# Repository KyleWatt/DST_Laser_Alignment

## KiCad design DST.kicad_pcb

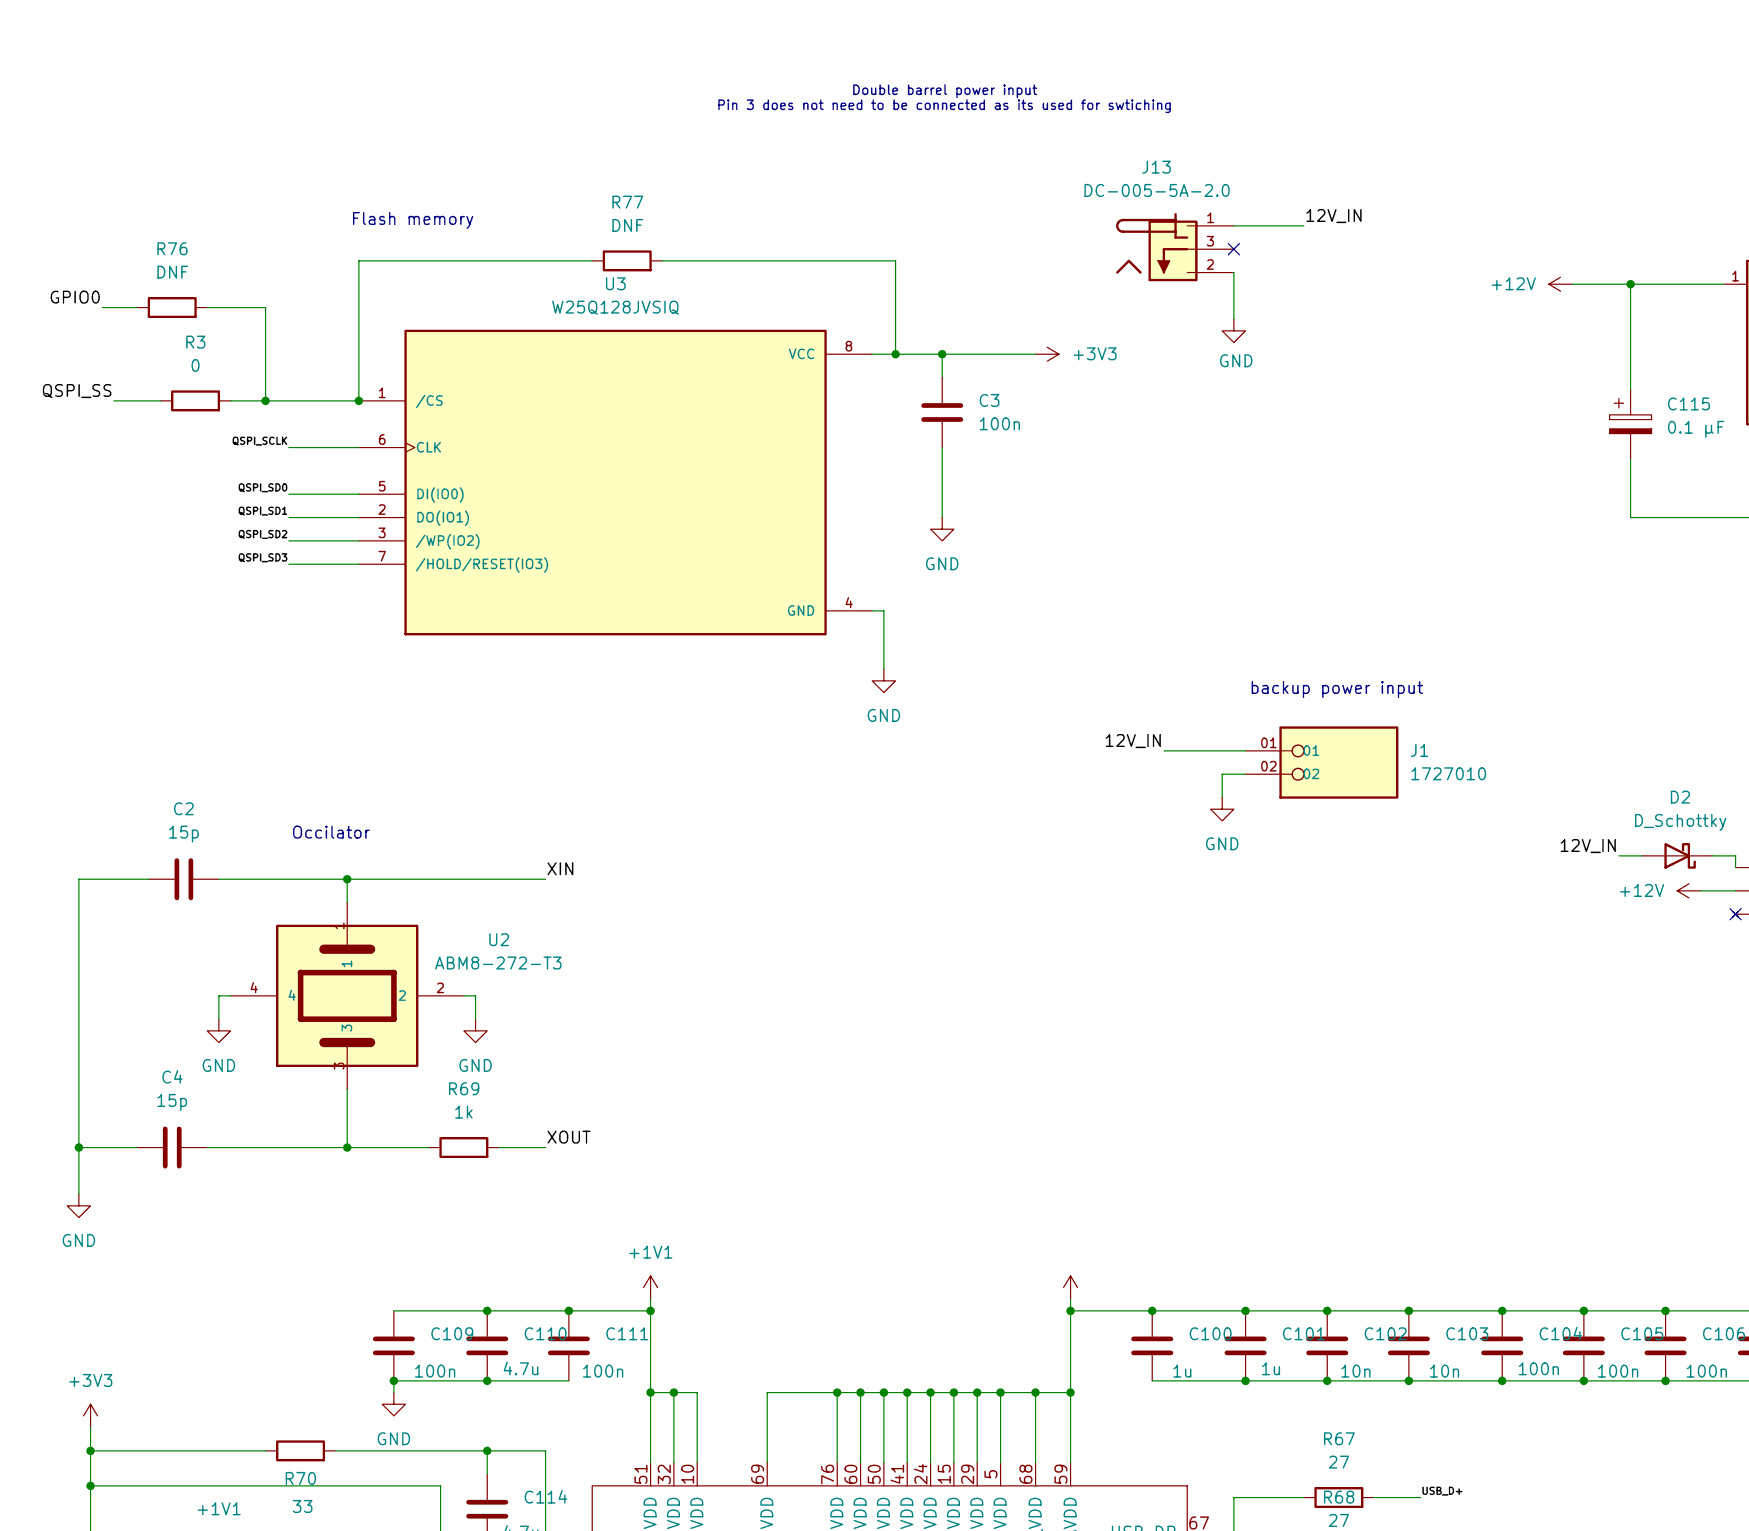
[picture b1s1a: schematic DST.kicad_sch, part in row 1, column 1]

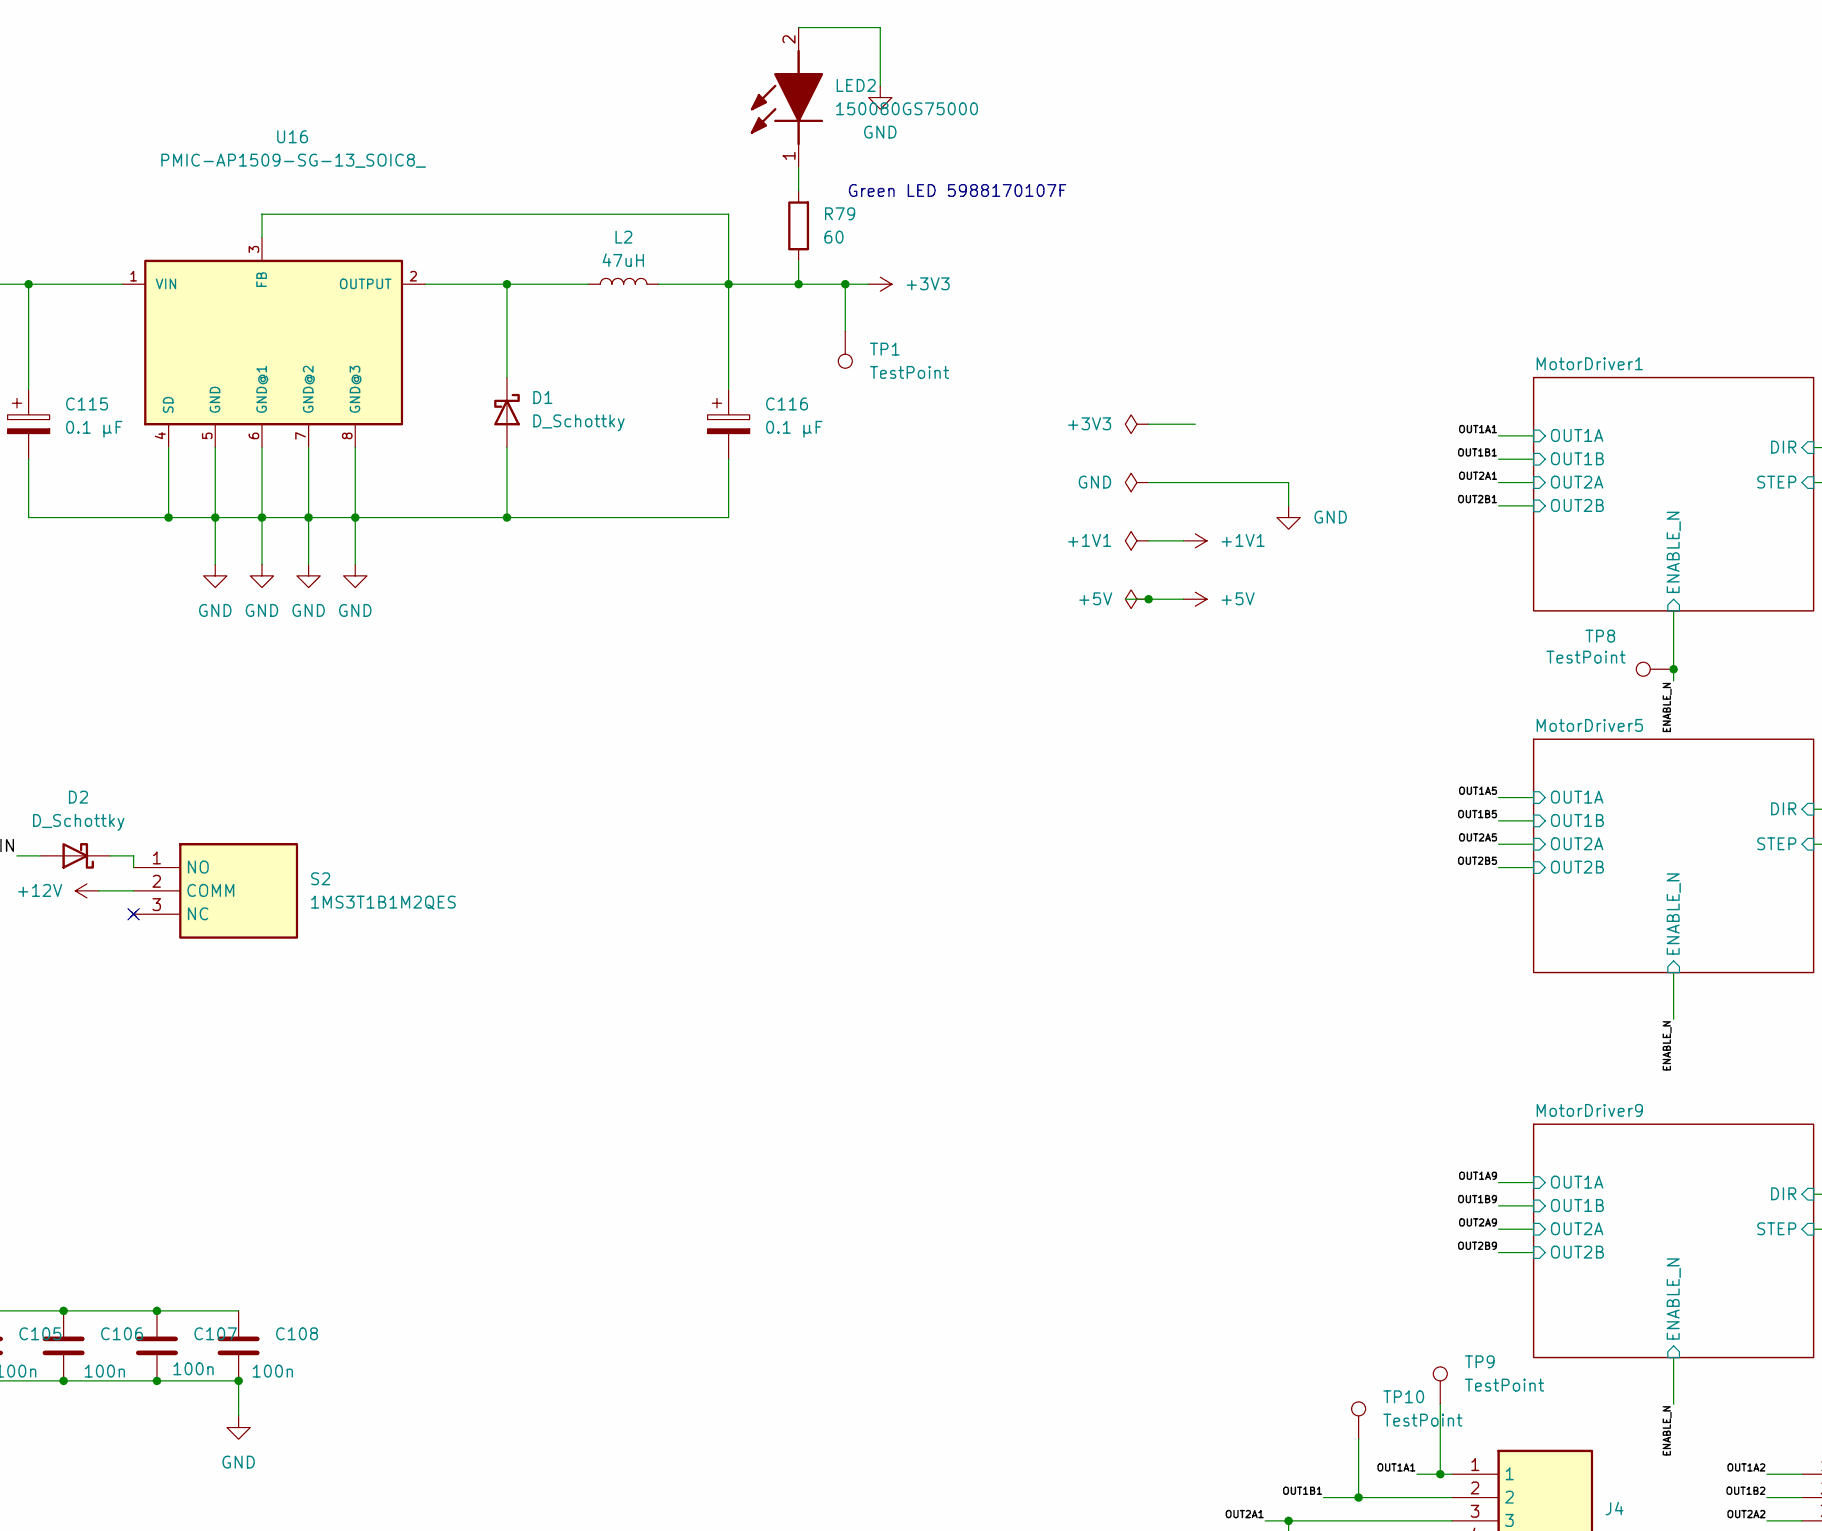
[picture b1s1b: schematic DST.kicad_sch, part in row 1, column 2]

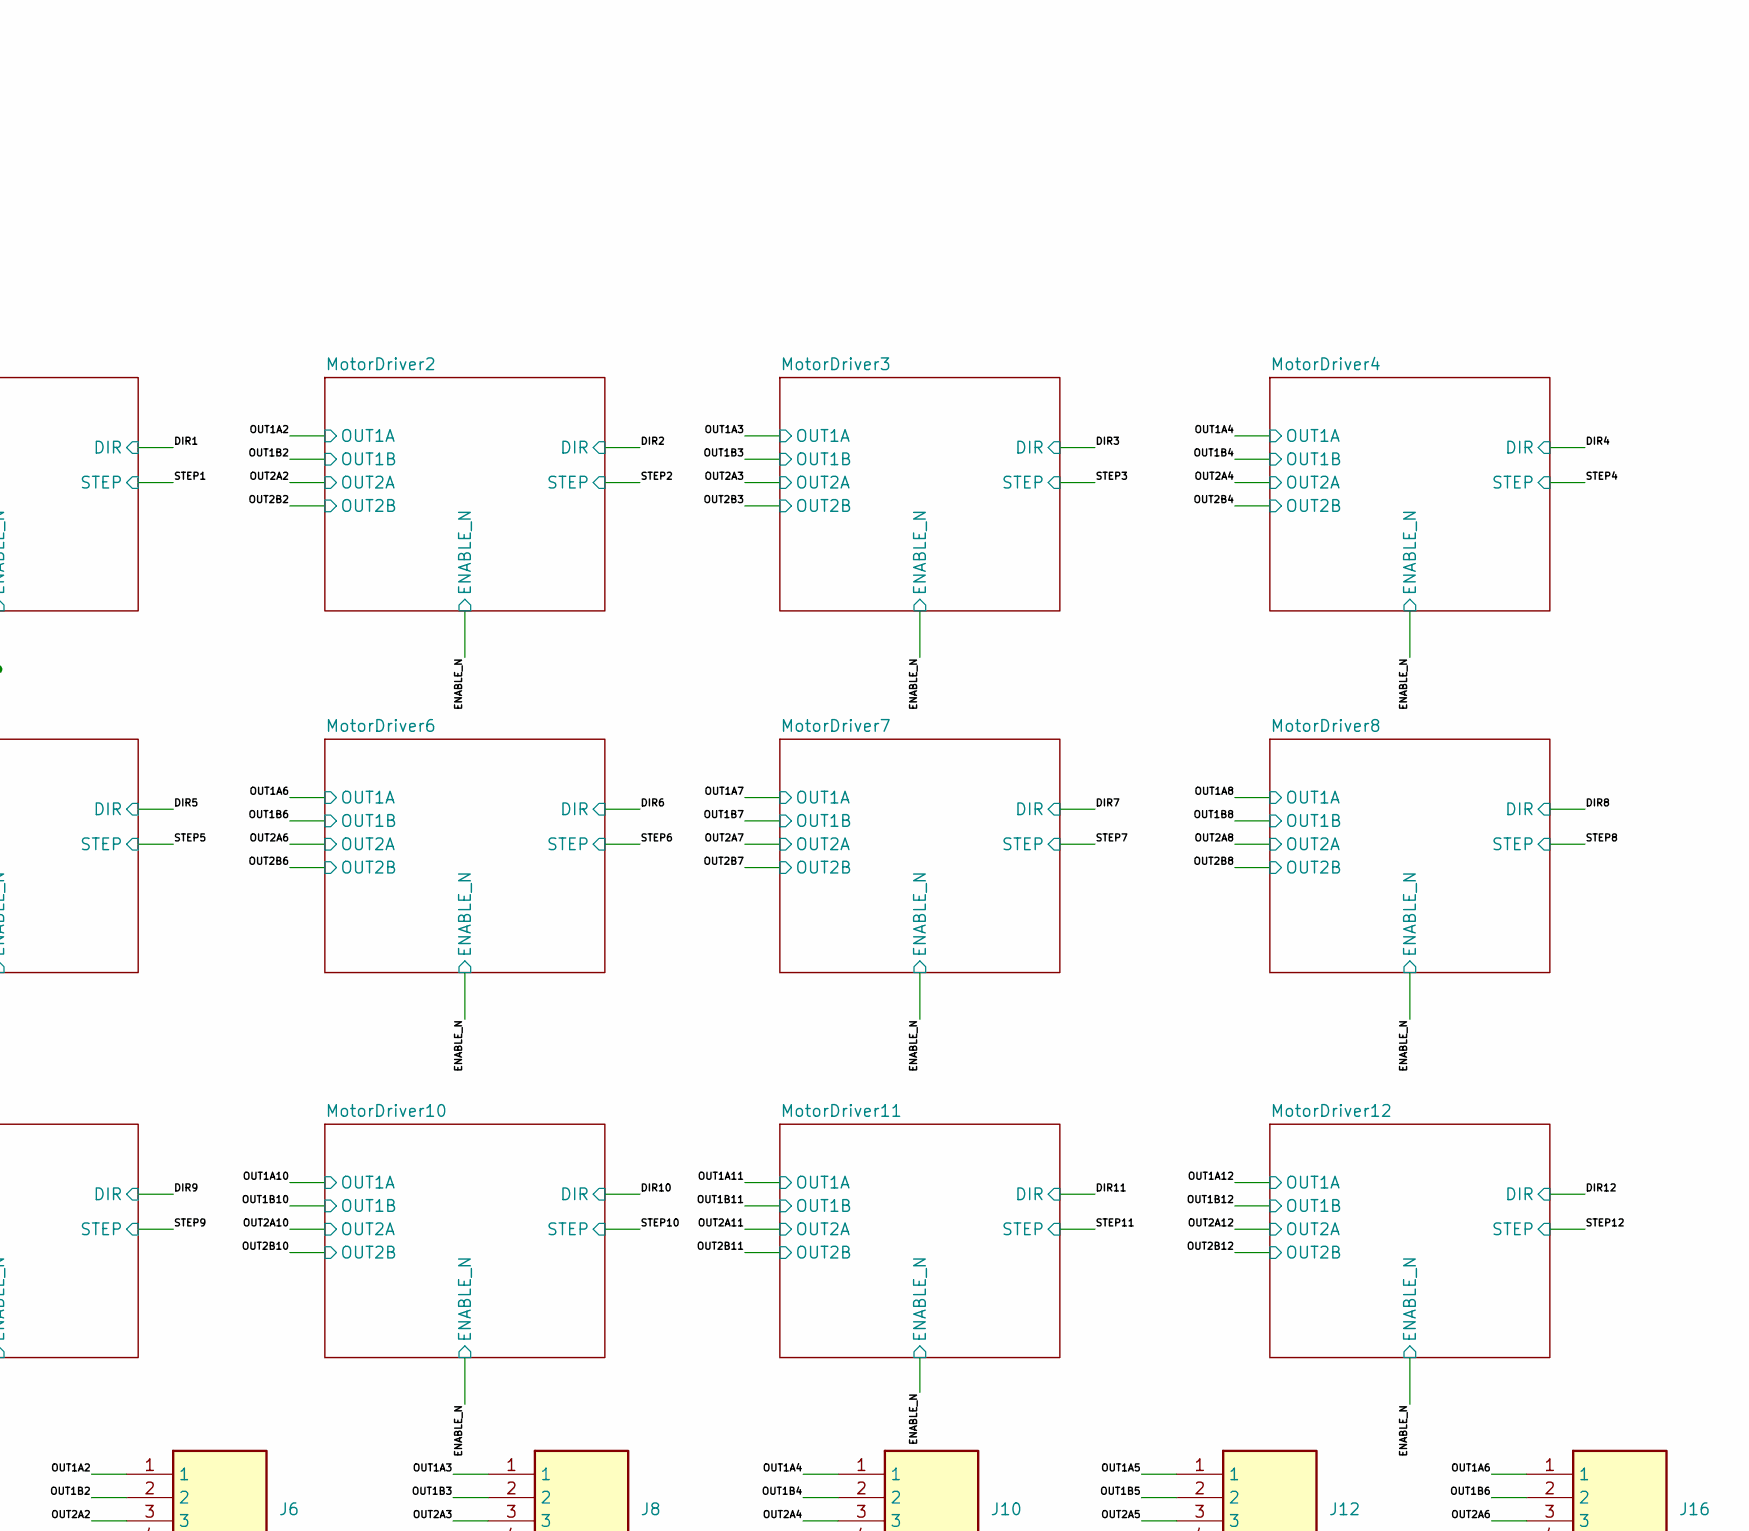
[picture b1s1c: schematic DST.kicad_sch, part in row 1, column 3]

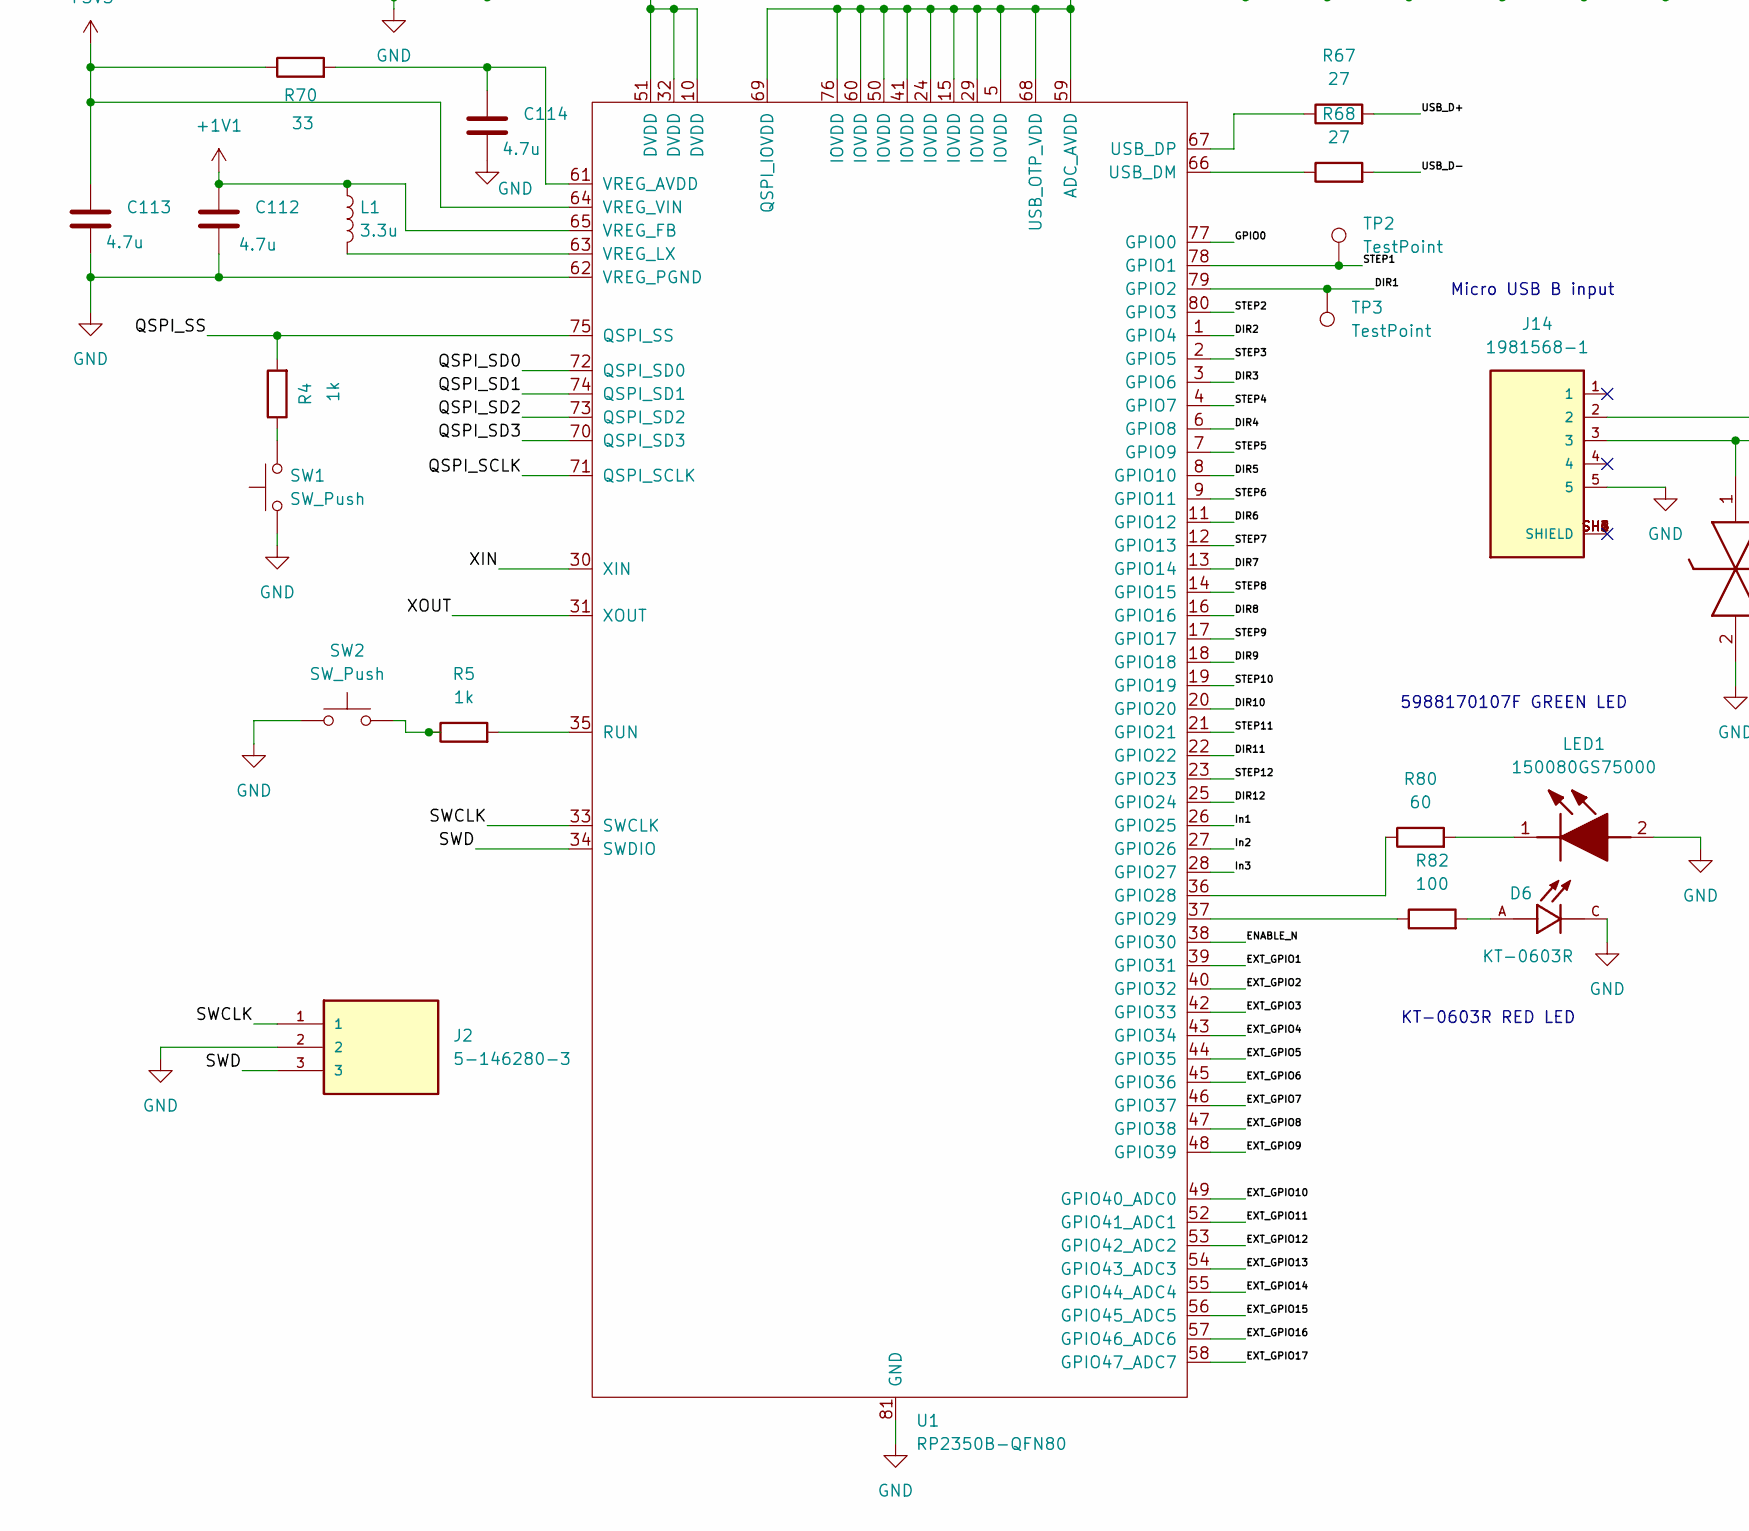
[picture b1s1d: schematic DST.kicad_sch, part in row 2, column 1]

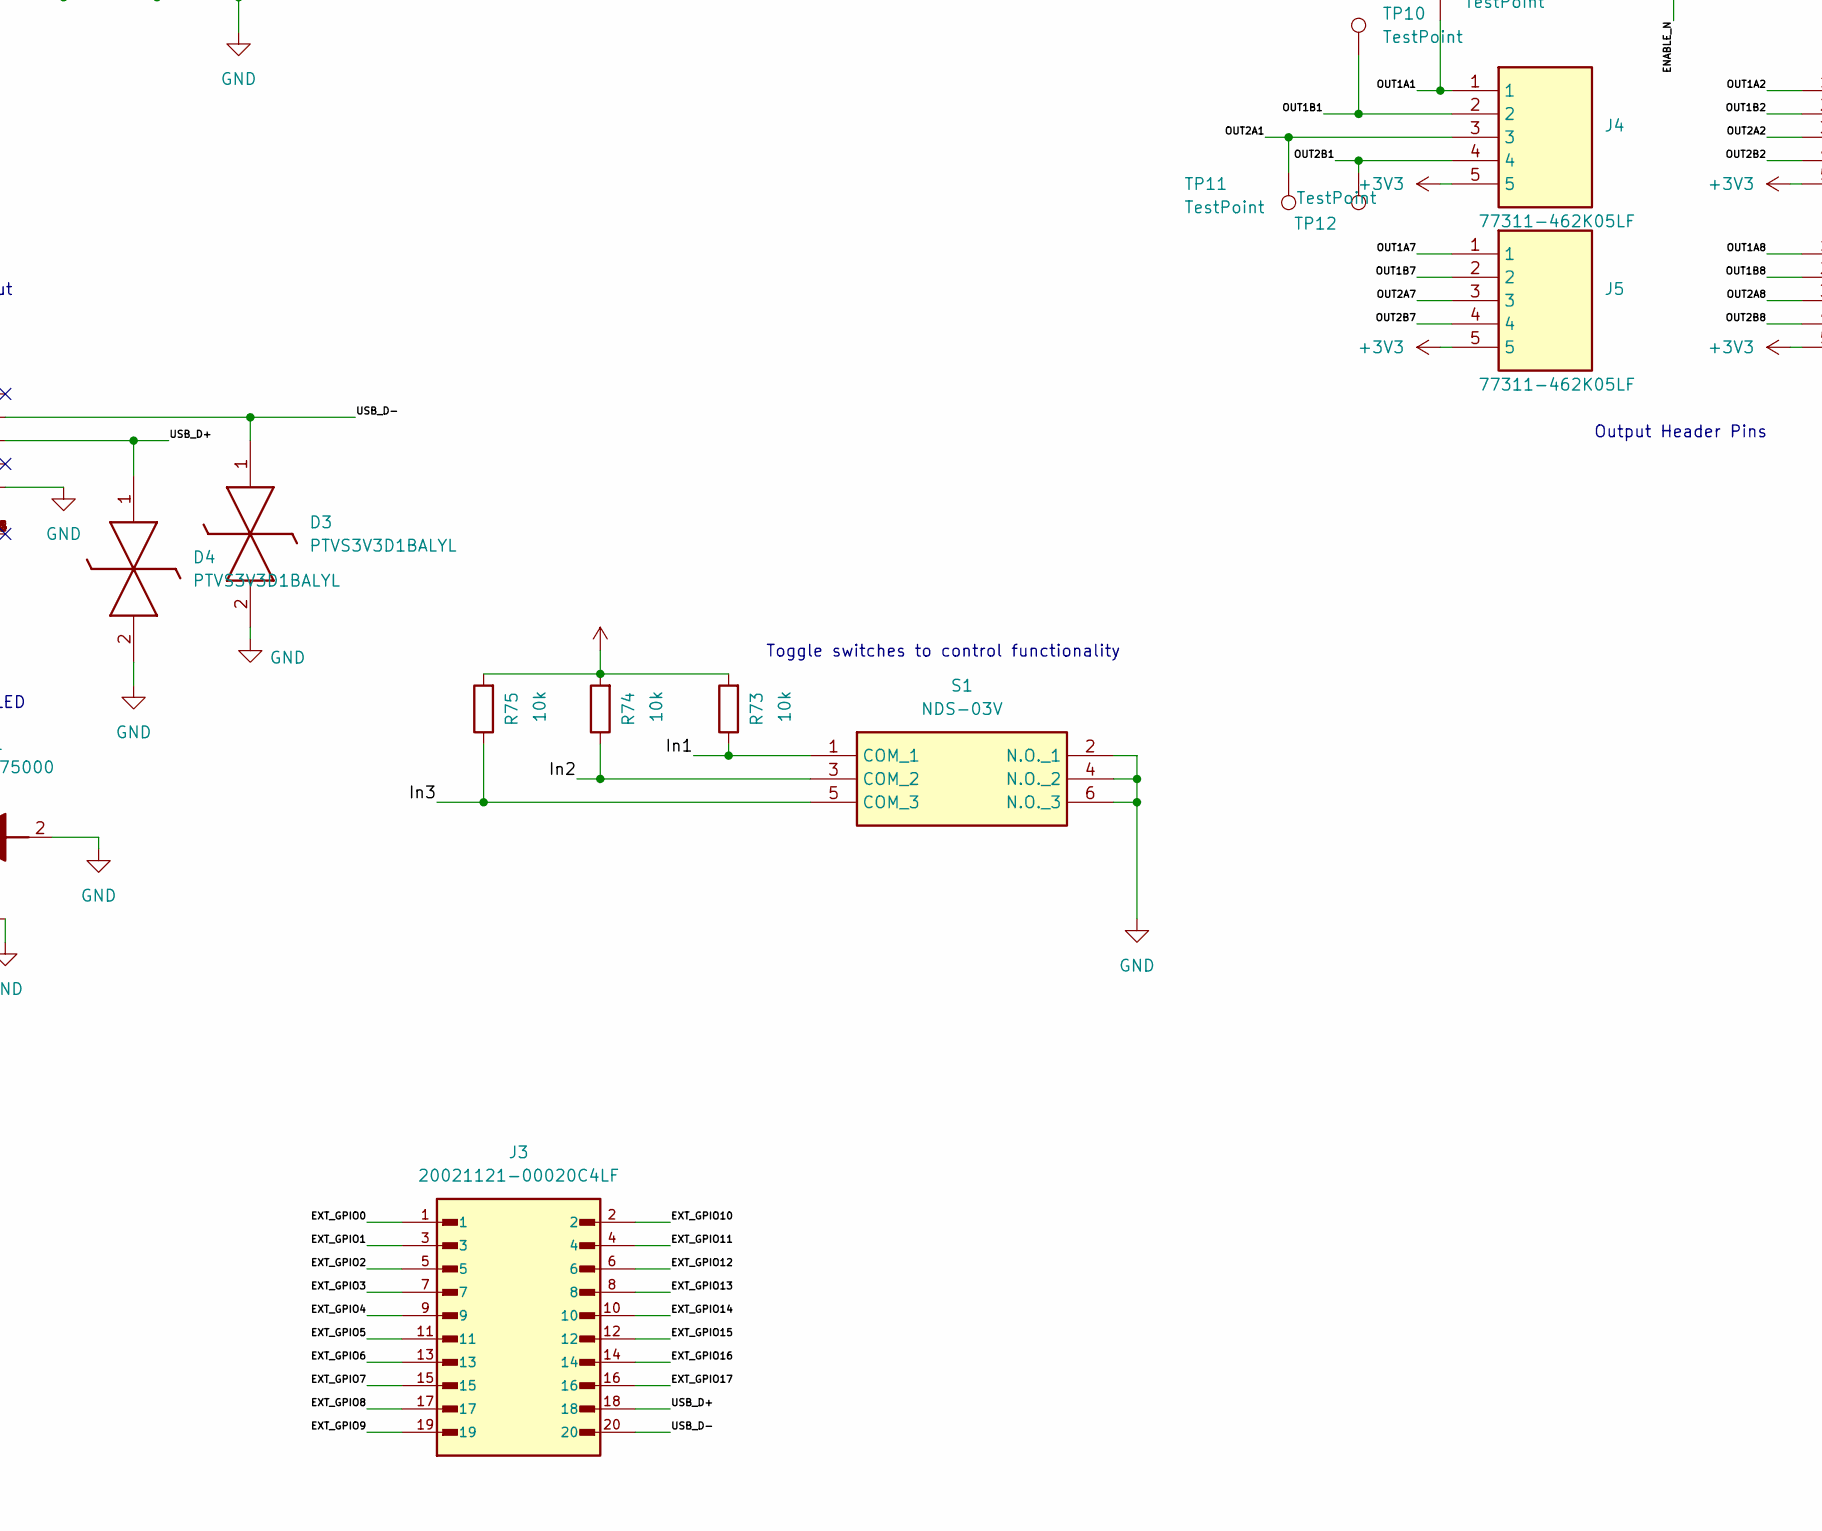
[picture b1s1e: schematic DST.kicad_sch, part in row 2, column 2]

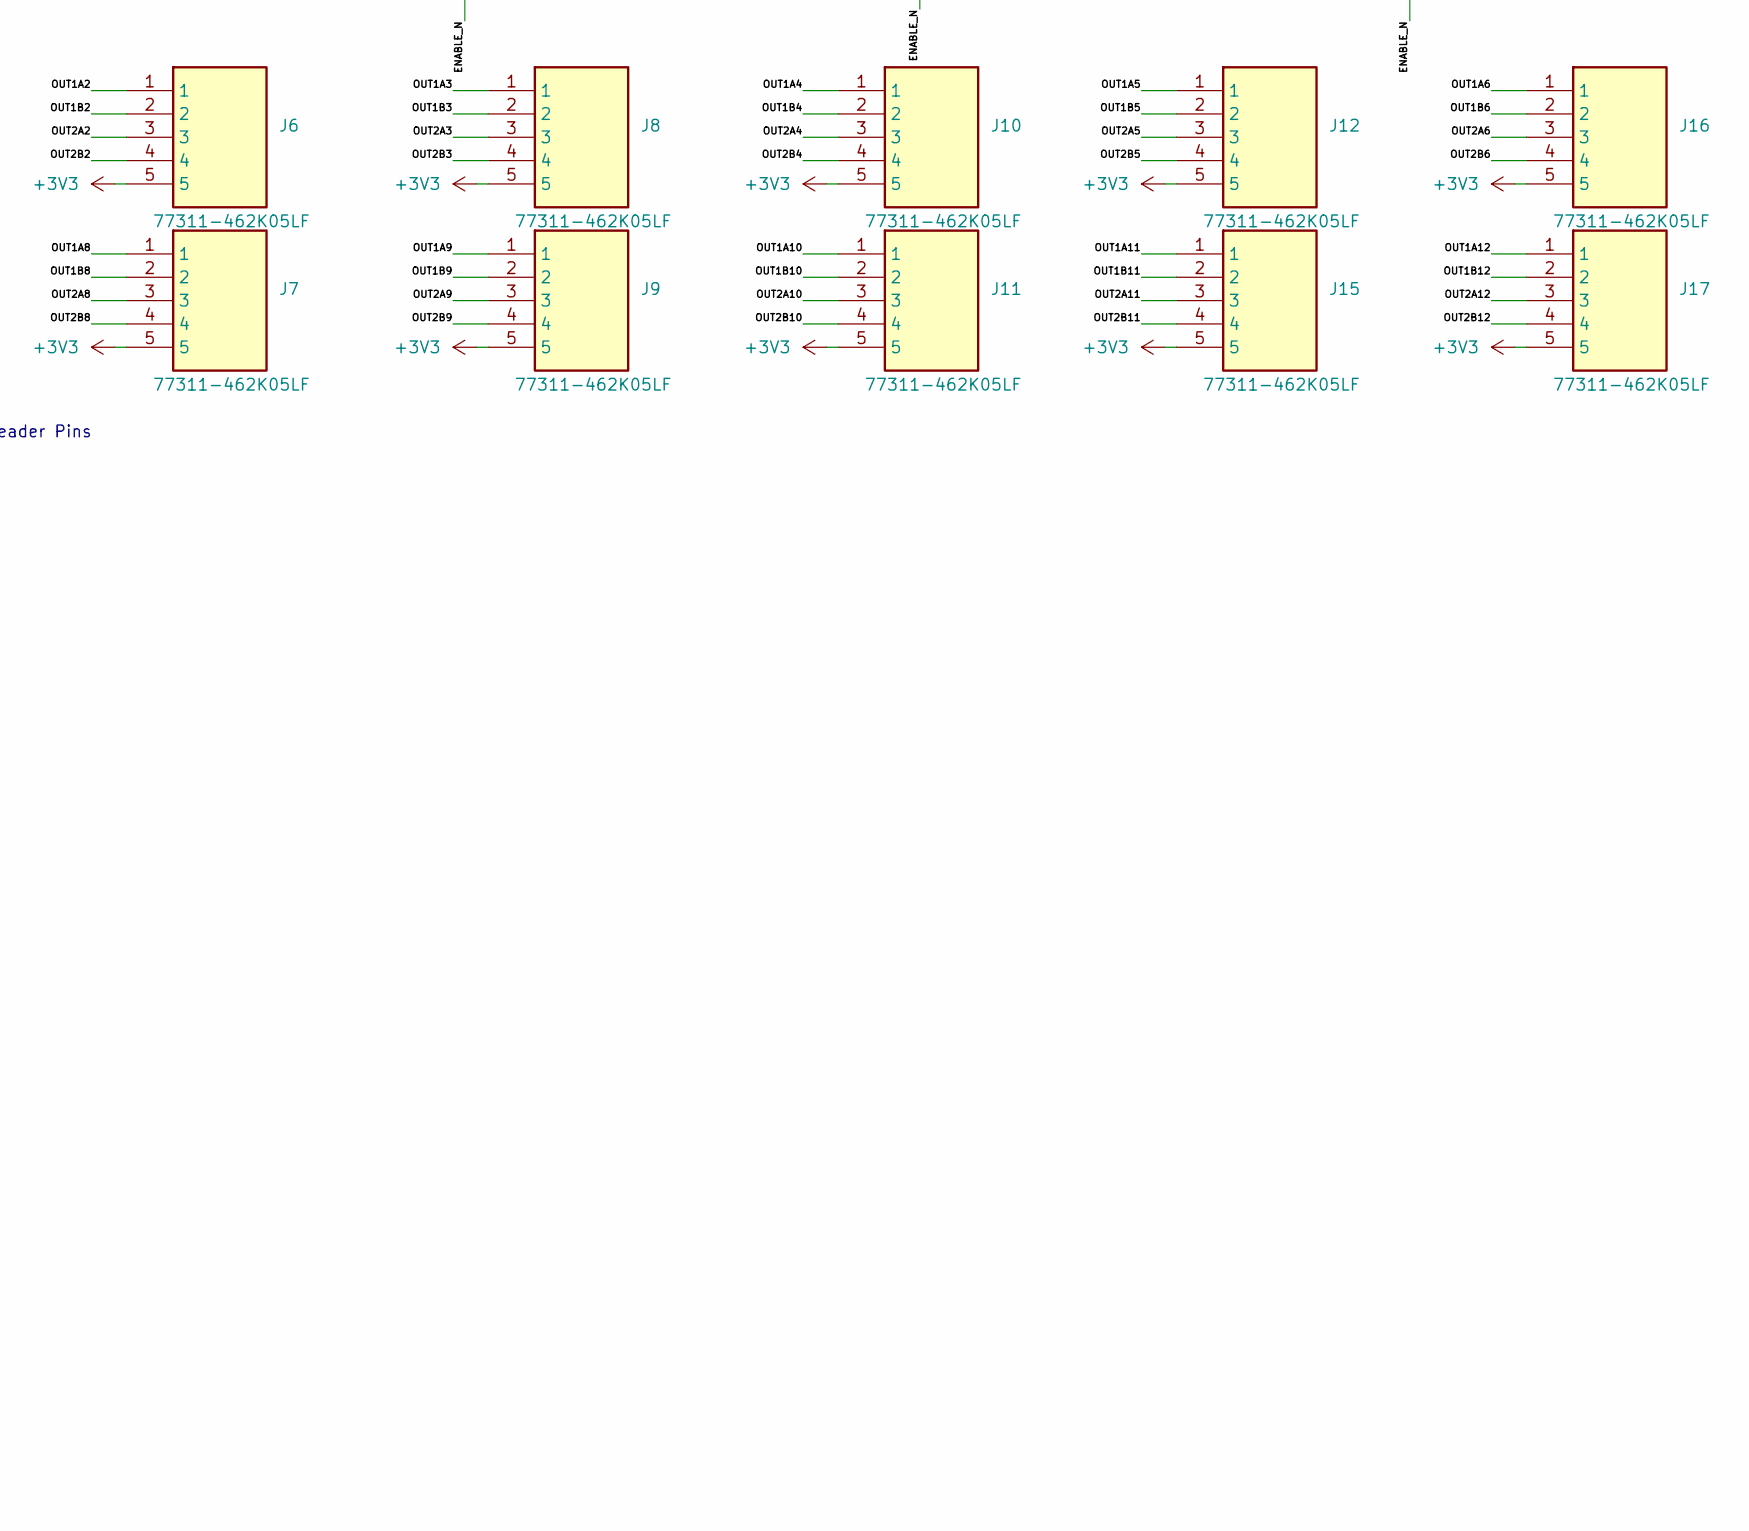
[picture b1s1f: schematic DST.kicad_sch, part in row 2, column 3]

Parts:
C2, C4: 15p; C_0402_1005Metric
C3, C104, C105, C106, C107, C108, C109, C111: 100n; C_0402_1005Metric
C100, C101: 1u; C_0402_1005Metric
C102, C103: 10n; C_0402_1005Metric
C110, C112, C113, C114: 4.7u; C_0402_1005Metric
C115, C116: 0.1 µF; C_0603_1608Metric
D1, D2: D_Schottky; DIOM5436X244N
D3, D4: PTVS3V3D1BALYL; PESD5V0S1BL315; Mouser Part Number 771-PTVS3V3D1BALYL
D6: KT-0603R; LED_KT-0603R; PARTREV 2013/01/24
J1: 1727010; PHOENIX_1727010; PARTREV 03.03.2021
J2: 5-146280-3; TE_5-146280-3; PARTREV R
J3: 20021121-00020C4LF; AMPHENOL_20021121-00020C4LF
J4, J5, J6, J7, J8, J9, J10, J11, J12, J15, J16, J17: 77311-462K05LF; HDRV5W62P0X254_1X5_1270X240X1624P; Manufacturer_Part_Number 77311-462K05LF
J13: DC-005-5A-2.0; XKB_DC-005-5A-2.0; PARTREV A0
J14: 1981568-1; TE_1981568-1; PARTREV E3
L1: 3.3u; L_0402_1005Metric
L2: 47uH; L_0805_2012Metric
LED1, LED2: 150080GS75000; LEDM2012X80N; Mouser Part Number 710-150080GS75000
R3: 0; R_0805_2012Metric
R4, R5, R69: 1k; R_0805_2012Metric
R67, R68: 27; R_0402_1005Metric
R70: 33; R_0805_2012Metric
R73, R74, R75: 10k; R_0402_1005Metric
R76, R77: DNF; R_0805_2012Metric
R79: 60; R_0805_2012Metric
R80: 60; R_0402_1005Metric
R82: 100; R_0402_1005Metric
S1: NDS-03V; NDS03V; Mouser Part Number 113-NDS03V
S2: 1MS3T1B1M2QES; Mouser Part Number 118-1MS3T1B1M2QES
SW1, SW2: SW_Push; SPEH110101
TP1, TP2, TP3, TP8, TP9, TP10, TP11, TP12: TestPoint; TestPoint_Pad_2.0x2.0mm
U1: RP2350B-QFN80; QFN-80-1EP_10x10mm_P0.4mm_EP3.4x3.4mm_ThermalVias
U2: ABM8-272-T3
U3: W25Q128JVSIQ; SOIC127P790X216-8N; PARTREV I
U16: PMIC-AP1509-SG-13_SOIC8_; SOIC8-1.27-5X4MM; MPN AP1509-SG-13

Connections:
+1V1: C109.2, C110.2, C111.2, C112.2, L1.1, U1.10 (DVDD), U1.32 (DVDD), U1.51 (DVDD), U1.65 (VREG_FB)
+3V3: C3.1, C100.2, C101.2, C102.2, C103.2, C104.2, C105.2, C106.2, C107.2, C108.2, C113.2, C116.1, J4.5, J5.5, J6.5, J7.5, J8.5, J9.5, J10.5, J11.5, J12.5, J15.5, J16.5, J17.5, L2.2, R70.1, R73.2, R74.2, R75.2, R77.2, R79.1, TP1.1, U1.5 (IOVDD), U1.15 (IOVDD), U1.24 (IOVDD), U1.29 (IOVDD), U1.41 (IOVDD), U1.50 (IOVDD), U1.59 (ADC_AVDD), U1.60 (IOVDD), U1.64 (VREG_VIN), U1.68 (USB_OTP_VDD), U1.69 (QSPI_IOVDD), U1.76 (IOVDD), U3.8 (VCC), U16.3 (FB); also elsewhere on the board
/12V_IN: D2.2 (A), J1.01, J13.1
/DIR1: TP3.1, U1.79 (GPIO2); also elsewhere on the board
/DIR2: U1.1 (GPIO4); also elsewhere on the board
/DIR3: U1.3 (GPIO6); also elsewhere on the board
/DIR4: U1.6 (GPIO8); also elsewhere on the board
/DIR5: U1.8 (GPIO10); also elsewhere on the board
/DIR6: U1.11 (GPIO12); also elsewhere on the board
/DIR7: U1.13 (GPIO14); also elsewhere on the board
/DIR8: U1.16 (GPIO16); also elsewhere on the board
/DIR9: U1.18 (GPIO18); also elsewhere on the board
/DIR10: U1.20 (GPIO20); also elsewhere on the board
/DIR11: U1.22 (GPIO22); also elsewhere on the board
/DIR12: U1.25 (GPIO24); also elsewhere on the board
/ENABLE_N: TP8.1, U1.38 (GPIO30); also elsewhere on the board
/EXT_GPIO0: J3.1
/EXT_GPIO1: J3.3, U1.39 (GPIO31)
/EXT_GPIO2: J3.5, U1.40 (GPIO32)
/EXT_GPIO3: J3.7, U1.42 (GPIO33)
/EXT_GPIO4: J3.9, U1.43 (GPIO34)
/EXT_GPIO5: J3.11, U1.44 (GPIO35)
/EXT_GPIO6: J3.13, U1.45 (GPIO36)
/EXT_GPIO7: J3.15, U1.46 (GPIO37)
/EXT_GPIO8: J3.17, U1.47 (GPIO38)
/EXT_GPIO9: J3.19, U1.48 (GPIO39)
/EXT_GPIO10: J3.2, U1.49 (GPIO40_ADC0)
/EXT_GPIO11: J3.4, U1.52 (GPIO41_ADC1)
/EXT_GPIO12: J3.6, U1.53 (GPIO42_ADC2)
/EXT_GPIO13: J3.8, U1.54 (GPIO43_ADC3)
/EXT_GPIO14: J3.10, U1.55 (GPIO44_ADC4)
/EXT_GPIO15: J3.12, U1.56 (GPIO45_ADC5)
/EXT_GPIO16: J3.14, U1.57 (GPIO46_ADC6)
/EXT_GPIO17: J3.16, U1.58 (GPIO47_ADC7)
/GPIO0: R76.1, U1.77 (GPIO0)
/In1: R73.1, S1.1 (COM_1), U1.26 (GPIO25)
/In2: R74.1, S1.3 (COM_2), U1.27 (GPIO26)
/In3: R75.1, S1.5 (COM_3), U1.28 (GPIO27)
/OUT1A1: J4.1, TP9.1; also elsewhere on the board
/OUT1A2: J6.1; also elsewhere on the board
/OUT1A3: J8.1; also elsewhere on the board
/OUT1A4: J10.1; also elsewhere on the board
/OUT1A5: J12.1; also elsewhere on the board
/OUT1A6: J16.1; also elsewhere on the board
/OUT1A7: J5.1; also elsewhere on the board
/OUT1A8: J7.1; also elsewhere on the board
/OUT1A9: J9.1; also elsewhere on the board
/OUT1A10: J11.1; also elsewhere on the board
/OUT1A11: J15.1; also elsewhere on the board
/OUT1A12: J17.1; also elsewhere on the board
/OUT1B1: J4.2, TP10.1; also elsewhere on the board
/OUT1B2: J6.2; also elsewhere on the board
/OUT1B3: J8.2; also elsewhere on the board
/OUT1B4: J10.2; also elsewhere on the board
/OUT1B5: J12.2; also elsewhere on the board
/OUT1B6: J16.2; also elsewhere on the board
/OUT1B7: J5.2; also elsewhere on the board
/OUT1B8: J7.2; also elsewhere on the board
/OUT1B9: J9.2; also elsewhere on the board
/OUT1B10: J11.2; also elsewhere on the board
/OUT1B11: J15.2; also elsewhere on the board
/OUT1B12: J17.2; also elsewhere on the board
/OUT2A1: J4.3, TP11.1; also elsewhere on the board
/OUT2A2: J6.3; also elsewhere on the board
/OUT2A3: J8.3; also elsewhere on the board
/OUT2A4: J10.3; also elsewhere on the board
/OUT2A5: J12.3; also elsewhere on the board
/OUT2A6: J16.3; also elsewhere on the board
/OUT2A7: J5.3; also elsewhere on the board
/OUT2A8: J7.3; also elsewhere on the board
/OUT2A9: J9.3; also elsewhere on the board
/OUT2A10: J11.3; also elsewhere on the board
/OUT2A11: J15.3; also elsewhere on the board
/OUT2A12: J17.3; also elsewhere on the board
/OUT2B1: J4.4, TP12.1; also elsewhere on the board
/OUT2B2: J6.4; also elsewhere on the board
/OUT2B3: J8.4; also elsewhere on the board
/OUT2B4: J10.4; also elsewhere on the board
/OUT2B5: J12.4; also elsewhere on the board
/OUT2B6: J16.4; also elsewhere on the board
/OUT2B7: J5.4; also elsewhere on the board
/OUT2B8: J7.4; also elsewhere on the board
/OUT2B9: J9.4; also elsewhere on the board
/OUT2B10: J11.4; also elsewhere on the board
/OUT2B11: J15.4; also elsewhere on the board
/OUT2B12: J17.4; also elsewhere on the board
/QSPI_SCLK: U1.71 (QSPI_SCLK), U3.6 (CLK)
/QSPI_SD0: U1.72 (QSPI_SD0), U3.5 (DI(IO0))
/QSPI_SD1: U1.74 (QSPI_SD1), U3.2 (DO(IO1))
/QSPI_SD2: U1.73 (QSPI_SD2), U3.3 (/WP(IO2))
/QSPI_SD3: U1.70 (QSPI_SD3), U3.7 (/HOLD/RESET(IO3))
/QSPI_SS: R3.1, R4.2, U1.75 (QSPI_SS)
/STEP1: TP2.1, U1.78 (GPIO1); also elsewhere on the board
/STEP2: U1.80 (GPIO3); also elsewhere on the board
/STEP3: U1.2 (GPIO5); also elsewhere on the board
/STEP4: U1.4 (GPIO7); also elsewhere on the board
/STEP5: U1.7 (GPIO9); also elsewhere on the board
/STEP6: U1.9 (GPIO11); also elsewhere on the board
/STEP7: U1.12 (GPIO13); also elsewhere on the board
/STEP8: U1.14 (GPIO15); also elsewhere on the board
/STEP9: U1.17 (GPIO17); also elsewhere on the board
/STEP10: U1.19 (GPIO19); also elsewhere on the board
/STEP11: U1.21 (GPIO21); also elsewhere on the board
/STEP12: U1.23 (GPIO23); also elsewhere on the board
/SWCLK: J2.1, U1.33 (SWCLK)
/SWD: J2.3, U1.34 (SWDIO)
/USB_D+: D4.1 (K1), J3.18, J14.3, R67.2
/USB_D-: D3.1 (K1), J3.20, J14.2, R68.2
/XIN: C2.2, U1.30 (XIN), U2.1
/XOUT: R69.2, U1.31 (XOUT)
GND: C2.1, C3.2, C4.1, C100.1, C101.1, C102.1, C103.1, C104.1, C105.1, C106.1, C107.1, C108.1, C109.1, C110.1, C111.1, C112.1, C113.1, C114.1, C115.2, C116.2, D1.2 (A), D3.2 (K2), D4.2 (K2), D6.C, J1.02, J2.2, J13.2, J14.5, LED1.2 (A), LED2.2 (A), S1.2 (N.O._1), S1.4 (N.O._2), S1.6 (N.O._3), SW1.1, SW2.1, U1.62 (VREG_PGND), U1.81 (GND), U2.2, U2.4, U3.4 (GND), U16.4 (SD), U16.5 (GND), U16.6 (GND@1), U16.7 (GND@2), U16.8 (GND@3); also elsewhere on the board
unnamed: C4.2, R69.1, U2.3
unnamed: D1.1 (K), L2.1, U16.2 (OUTPUT)
unnamed: D6.A, R82.2
unnamed: LED1.1 (K), R80.2
unnamed: LED2.1 (K), R79.2
unnamed: R4.1, SW1.2
unnamed: R5.1, SW2.2
unnamed: R80.1, U1.36 (GPIO28)
unnamed: R82.1, U1.37 (GPIO29)
unnamed: R5.2, U1.35 (RUN)
unnamed: R68.1, U1.66 (USB_DM)
unnamed: R67.1, U1.67 (USB_DP)
unnamed: C114.2, R70.2, U1.61 (VREG_AVDD)
unnamed: L1.2, U1.63 (VREG_LX)
unnamed: R3.2, R76.2, R77.1, U3.1 (/CS)

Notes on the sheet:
5988170107F GREEN LED
backup power input
Toggle switches to control functionality
Output Header Pins
Micro USB B input
Double barrel power input Pin 3 does not need to be connected as its used for swtiching
KT-0603R RED LED
Flash memory
Occilator
Green LED 5988170107F
